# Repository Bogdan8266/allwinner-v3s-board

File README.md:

# allwinner-v3s-board
# allwinner-v3s-board

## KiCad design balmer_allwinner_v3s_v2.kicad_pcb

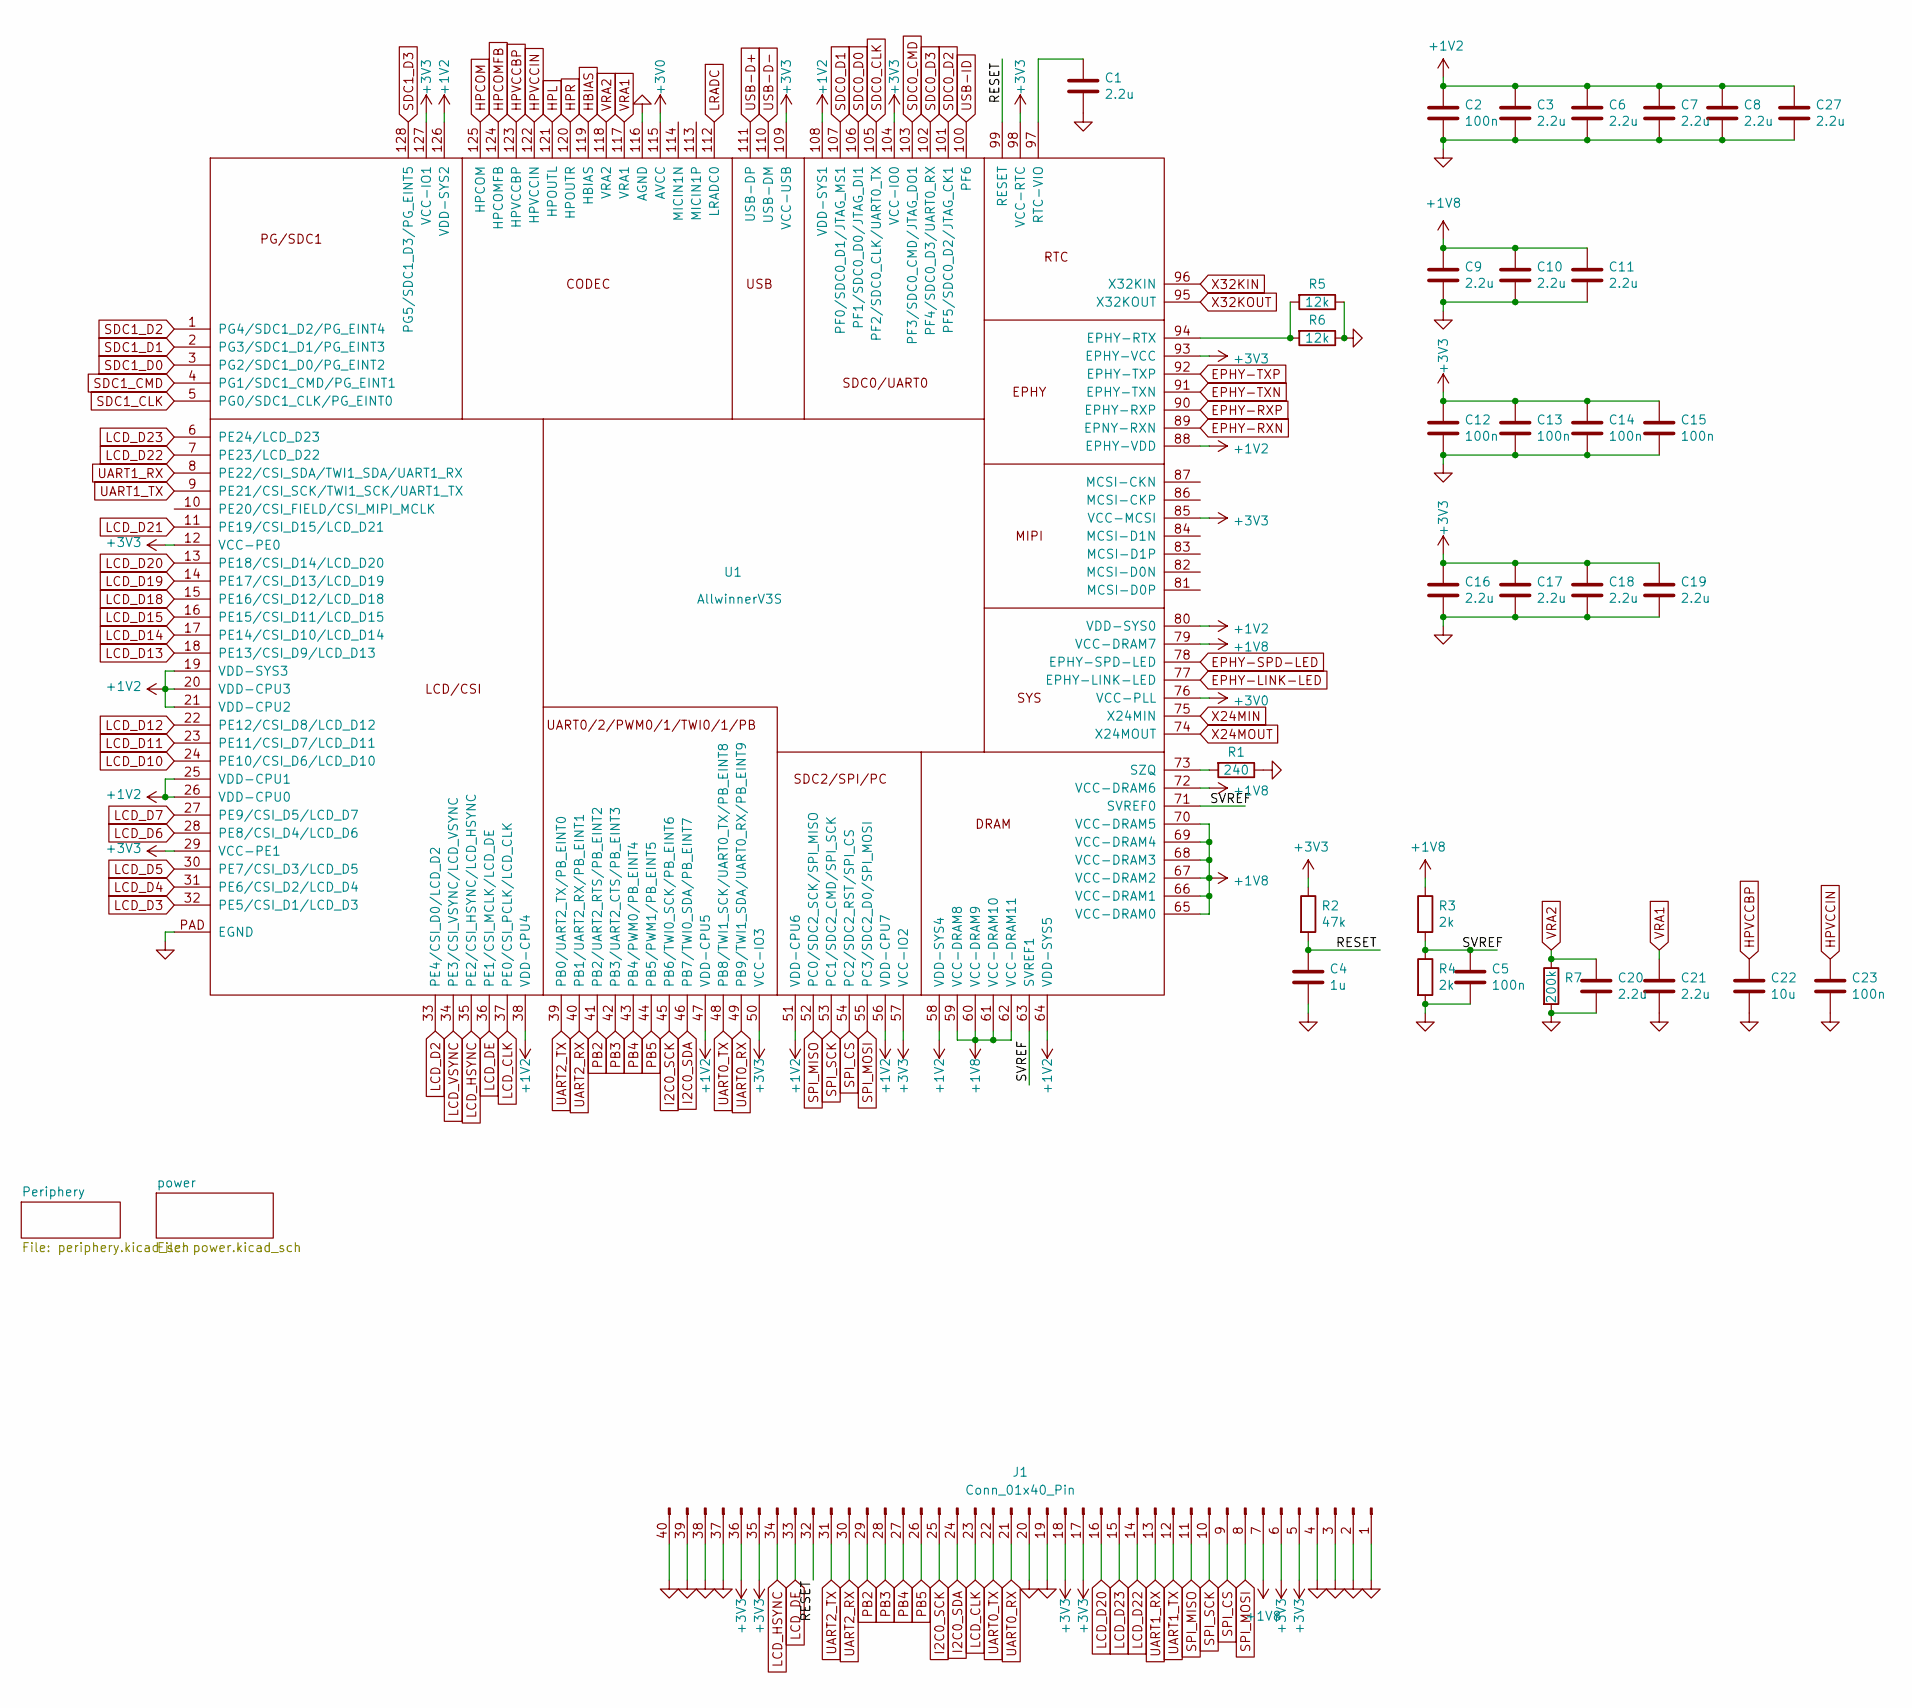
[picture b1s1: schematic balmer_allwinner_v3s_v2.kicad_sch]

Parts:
C1, C3, C6, C7, C8, C9, C10, C11, C16, C17, C18, C19, C20, C21, C27: 2.2u; C_0805_2012Metric
C2, C5, C12, C13, C14, C15, C23: 100n; C_0603_1608Metric
C4: 1u; C_0603_1608Metric
C22: 10u; C_0805_2012Metric
J1: Conn_01x40_Pin; DIP-40_100
R1: 240; R_0603_1608Metric
R2: 47k; R_0603_1608Metric
R3, R4: 2k; R_0603_1608Metric
R5, R6: 12k; R_0603_1608Metric
R7: 200k; R_0603_1608Metric
U1: AllwinnerV3S; eLQFP-128_14x14_Pitch0.4mm_EPAD_5.72mm

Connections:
+1V2: C2.1, C3.1, C6.1, C7.1, C8.1, C27.1, U1.19 (VDD-SYS3), U1.20 (VDD-CPU3), U1.21 (VDD-CPU2), U1.25 (VDD-CPU1), U1.26 (VDD-CPU0), U1.38 (VDD-CPU4), U1.47 (VDD-CPU5), U1.51 (VDD-CPU6), U1.56 (VDD-CPU7), U1.58 (VDD-SYS4), U1.64 (VDD-SYS5), U1.80 (VDD-SYS0), U1.88 (EPHY-VDD), U1.108 (VDD-SYS1), U1.126 (VDD-SYS2); also elsewhere on the board
+1V8: C9.1, C10.1, C11.1, J1.7, R3.1, U1.59 (VCC-DRAM8), U1.60 (VCC-DRAM9), U1.61 (VCC-DRAM10), U1.62 (VCC-DRAM11), U1.65 (VCC-DRAM0), U1.66 (VCC-DRAM1), U1.67 (VCC-DRAM2), U1.68 (VCC-DRAM3), U1.69 (VCC-DRAM4), U1.70 (VCC-DRAM5), U1.72 (VCC-DRAM6), U1.79 (VCC-DRAM7); also elsewhere on the board
+3V0: U1.76 (VCC-PLL), U1.115 (AVCC); also elsewhere on the board
+3V3: C12.1, C13.1, C14.1, C15.1, C16.1, C17.1, C18.1, C19.1, J1.5, J1.6, J1.17, J1.18, J1.35, J1.36, R2.1, U1.12 (VCC-PE0), U1.29 (VCC-PE1), U1.50 (VCC-IO3), U1.57 (VCC-IO2), U1.85 (VCC-MCSI), U1.93 (EPHY-VCC), U1.98 (VCC-RTC), U1.104 (VCC-IO0), U1.109 (VCC-USB), U1.127 (VCC-IO1); also elsewhere on the board
/RESET: C4.1, J1.32, R2.2, U1.99 (RESET)
/SVREF: C5.1, R3.2, R4.1, U1.63 (SVREF1), U1.71 (SVREF0)
EPHY-LINK-LED: U1.77 (EPHY-LINK-LED); also elsewhere on the board
EPHY-RXN: U1.89 (EPNY-RXN); also elsewhere on the board
EPHY-RXP: U1.90 (EPHY-RXP); also elsewhere on the board
EPHY-SPD-LED: U1.78 (EPHY-SPD-LED); also elsewhere on the board
EPHY-TXN: U1.91 (EPHY-TXN); also elsewhere on the board
EPHY-TXP: U1.92 (EPHY-TXP); also elsewhere on the board
GND: C1.2, C2.2, C3.2, C4.2, C5.2, C6.2, C7.2, C8.2, C9.2, C10.2, C11.2, C12.2, C13.2, C14.2, C15.2, C16.2, C17.2, C18.2, C19.2, C20.2, C21.2, C22.2, C23.2, C27.2, J1.1, J1.2, J1.3, J1.4, J1.19, J1.20, J1.37, J1.38, J1.39, J1.40, R1.1, R4.2, R5.1, R6.1, R7.2, U1.116 (AGND), U1.PAD (EGND); also elsewhere on the board
HBIAS: U1.119 (HBIAS); also elsewhere on the board
HPCOM: U1.125 (HPCOM); also elsewhere on the board
HPCOMFB: U1.124 (HPCOMFB); also elsewhere on the board
HPL: U1.121 (HPOUTL); also elsewhere on the board
HPR: U1.120 (HPOUTR); also elsewhere on the board
HPVCCBP: C22.1, U1.123 (HPVCCBP)
HPVCCIN: C23.1, U1.122 (HPVCCIN)
I2C0_SCK: J1.25, U1.45 (PB6/TWI0_SCK/PB_EINT6)
I2C0_SDA: J1.24, U1.46 (PB7/TWI0_SDA/PB_EINT7)
LCD_CLK: J1.23, U1.37 (PE0/CSI_PCLK/LCD_CLK)
LCD_D2: U1.33 (PE4/CSI_D0/LCD_D2)
LCD_D3: U1.32 (PE5/CSI_D1/LCD_D3)
LCD_D4: U1.31 (PE6/CSI_D2/LCD_D4)
LCD_D5: U1.30 (PE7/CSI_D3/LCD_D5)
LCD_D6: U1.28 (PE8/CSI_D4/LCD_D6)
LCD_D7: U1.27 (PE9/CSI_D5/LCD_D7)
LCD_D10: U1.24 (PE10/CSI_D6/LCD_D10)
LCD_D11: U1.23 (PE11/CSI_D7/LCD_D11)
LCD_D12: U1.22 (PE12/CSI_D8/LCD_D12)
LCD_D13: U1.18 (PE13/CSI_D9/LCD_D13)
LCD_D14: U1.17 (PE14/CSI_D10/LCD_D14)
LCD_D15: U1.16 (PE15/CSI_D11/LCD_D15)
LCD_D18: U1.15 (PE16/CSI_D12/LCD_D18)
LCD_D19: U1.14 (PE17/CSI_D13/LCD_D19)
LCD_D20: J1.16, U1.13 (PE18/CSI_D14/LCD_D20)
LCD_D21: U1.11 (PE19/CSI_D15/LCD_D21)
LCD_D22: J1.14, U1.7 (PE23/LCD_D22)
LCD_D23: J1.15, U1.6 (PE24/LCD_D23)
LCD_DE: J1.33, U1.36 (PE1/CSI_MCLK/LCD_DE)
LCD_HSYNC: J1.34, U1.35 (PE2/CSI_HSYNC/LCD_HSYNC)
LCD_VSYNC: U1.34 (PE3/CSI_VSYNC/LCD_VSYNC)
LRADC: U1.112 (LRADC0); also elsewhere on the board
unnamed: R5.2, R6.2, U1.94 (EPHY-RTX)
unnamed: C1.1, U1.97 (RTC-VIO)
unnamed: R1.2, U1.73 (SZQ)
PB2: J1.29, U1.41 (PB2/UART2_RTS/PB_EINT2)
PB3: J1.28, U1.42 (PB3/UART2_CTS/PB_EINT3)
PB4: J1.27, U1.43 (PB4/PWM0/PB_EINT4)
PB5: J1.26, U1.44 (PB5/PWM1/PB_EINT5)
SDC0_CLK: U1.105 (PF2/SDC0_CLK/UART0_TX); also elsewhere on the board
SDC0_CMD: U1.103 (PF3/SDC0_CMD/JTAG_DO1); also elsewhere on the board
SDC0_D0: U1.106 (PF1/SDC0_D0/JTAG_DI1); also elsewhere on the board
SDC0_D1: U1.107 (PF0/SDC0_D1/JTAG_MS1); also elsewhere on the board
SDC0_D2: U1.101 (PF5/SDC0_D2/JTAG_CK1); also elsewhere on the board
SDC0_D3: U1.102 (PF4/SDC0_D3/UART0_RX); also elsewhere on the board
SDC1_CLK: U1.5 (PG0/SDC1_CLK/PG_EINT0)
SDC1_CMD: U1.4 (PG1/SDC1_CMD/PG_EINT1)
SDC1_D0: U1.3 (PG2/SDC1_D0/PG_EINT2)
SDC1_D1: U1.2 (PG3/SDC1_D1/PG_EINT3)
SDC1_D2: U1.1 (PG4/SDC1_D2/PG_EINT4)
SDC1_D3: U1.128 (PG5/SDC1_D3/PG_EINT5)
SPI_CS: J1.9, U1.54 (PC2/SDC2_RST/SPI_CS)
SPI_MISO: J1.11, U1.52 (PC0/SDC2_SCK/SPI_MISO)
SPI_MOSI: J1.8, U1.55 (PC3/SDC2_D0/SPI_MOSI)
SPI_SCK: J1.10, U1.53 (PC1/SDC2_CMD/SPI_SCK)
UART0_RX: J1.21, U1.49 (PB9/TWI1_SDA/UART0_RX/PB_EINT9)
UART0_TX: J1.22, U1.48 (PB8/TWI1_SCK/UART0_TX/PB_EINT8)
UART1_RX: J1.13, U1.8 (PE22/CSI_SDA/TWI1_SDA/UART1_RX)
UART1_TX: J1.12, U1.9 (PE21/CSI_SCK/TWI1_SCK/UART1_TX)
UART2_RX: J1.30, U1.40 (PB1/UART2_RX/PB_EINT1)
UART2_TX: J1.31, U1.39 (PB0/UART2_TX/PB_EINT0)
USB-D+: U1.111 (USB-DP); also elsewhere on the board
USB-D-: U1.110 (USB-DM); also elsewhere on the board
USB-ID: U1.100 (PF6)
VRA1: C21.1, U1.117 (VRA1)
VRA2: C20.1, R7.1, U1.118 (VRA2)
X24MIN: U1.75 (X24MIN); also elsewhere on the board
X24MOUT: U1.74 (X24MOUT); also elsewhere on the board
X32KIN: U1.96 (X32KIN); also elsewhere on the board
X32KOUT: U1.95 (X32KOUT); also elsewhere on the board

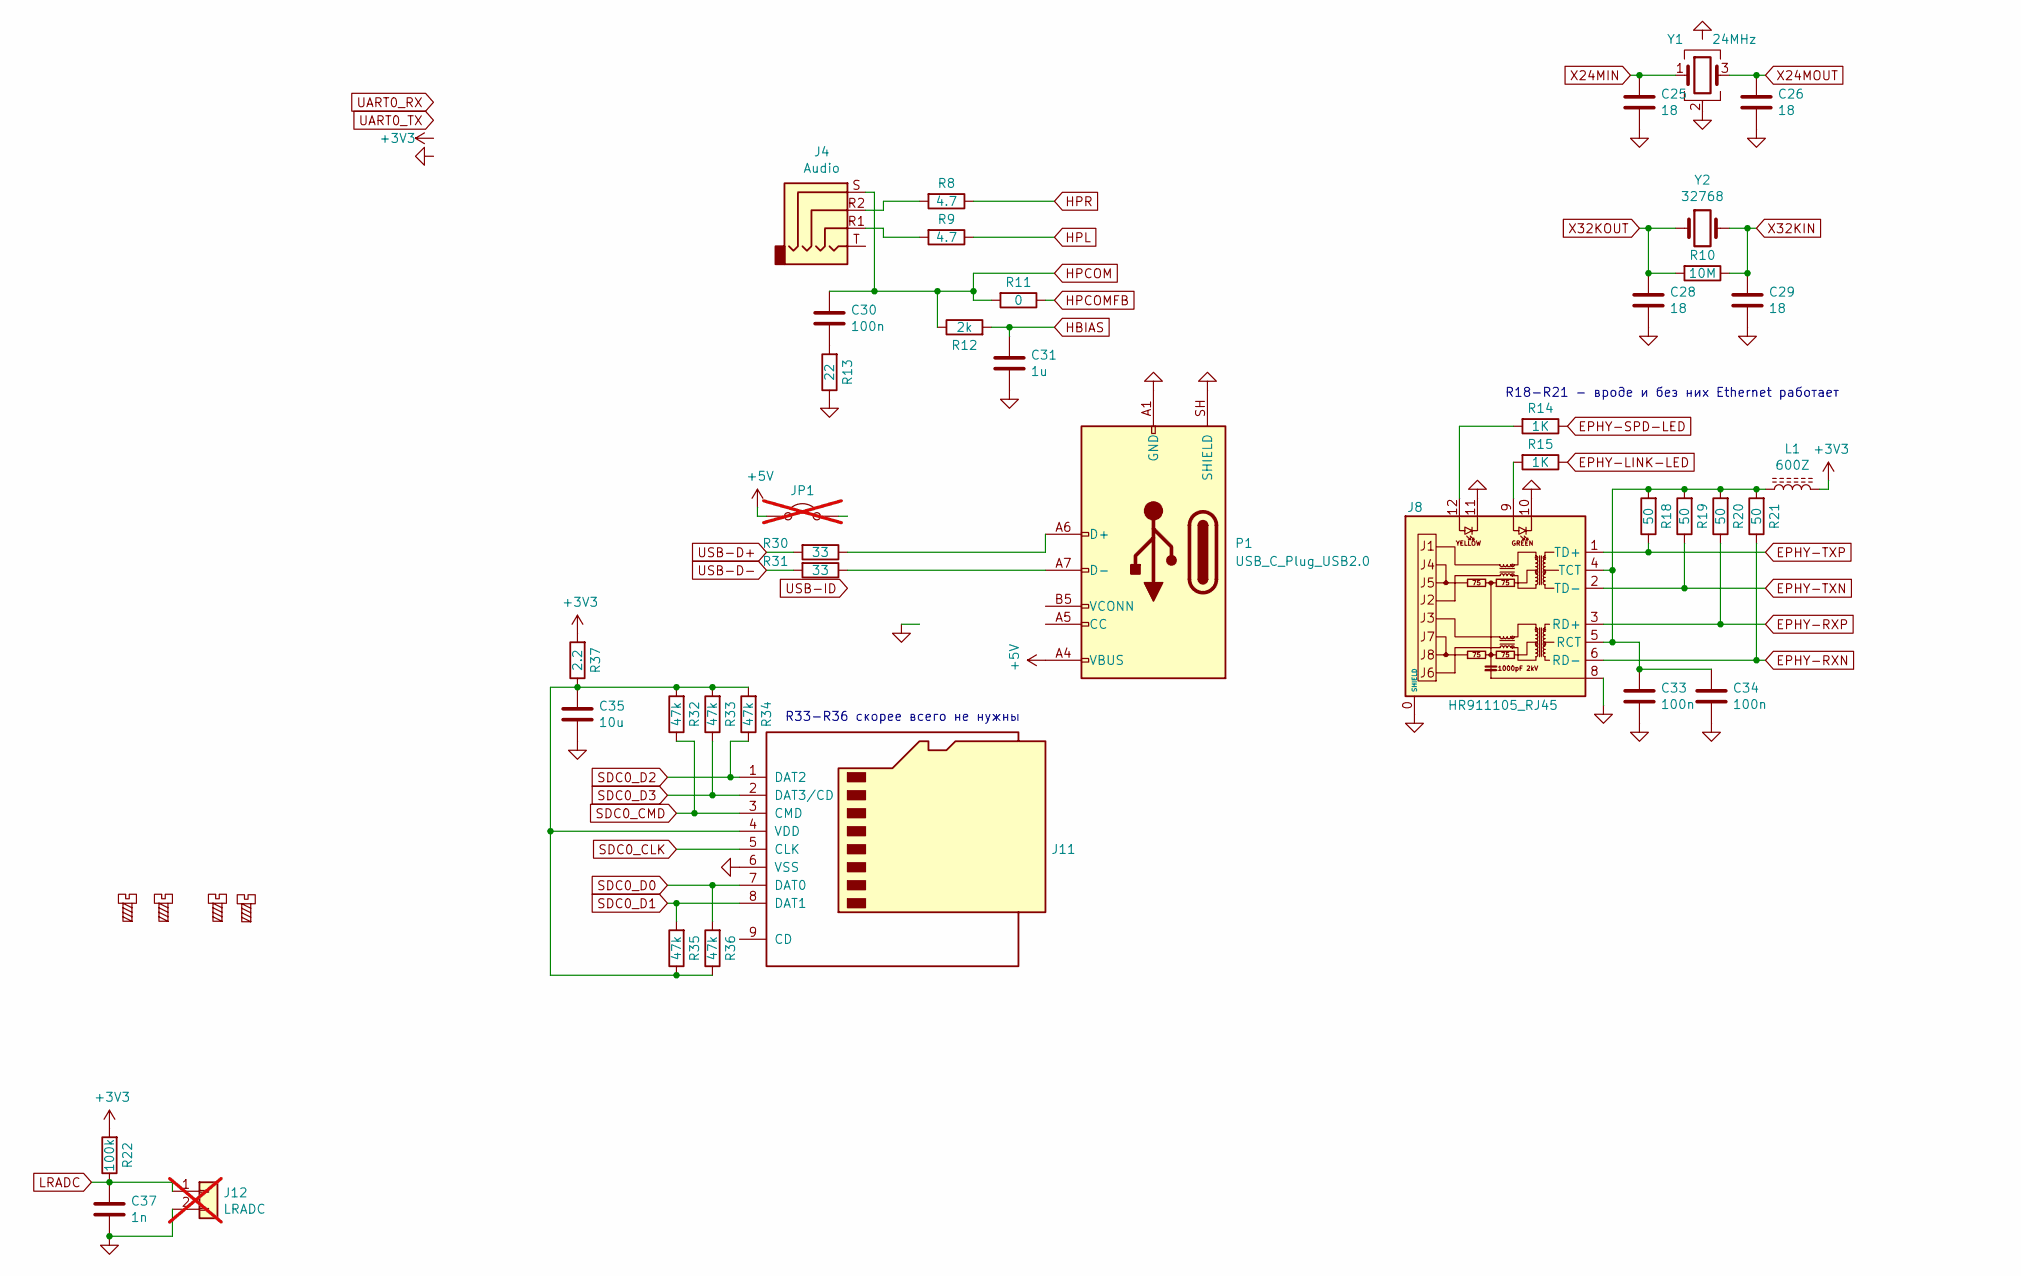
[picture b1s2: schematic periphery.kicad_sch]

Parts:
C25, C26, C28, C29: 18; C_0603_1608Metric
C30, C33, C34: 100n; C_0603_1608Metric
C31: 1u; C_0603_1608Metric
C35: 10u; C_1206_3216Metric
C37: 1n; C_0603_1608Metric
H1, H2, H3, H4: MountingScrew; MountingHole_2.5mm_Pad_Via
J4: Audio; Jack_3.5mm_PJ311_Horizontal
J8: HR911105_RJ45; HANRUN_HR911105A
J11: Micro_SD_Card_Ebay; microSD_HC_Wuerth_693072010801
J12: LRADC; PinSocket_1x02_P1.27mm_Vertical; not fitted
JP1: Jumper_2_Open; PinHeader_1x02_P2.00mm_Vertical; not fitted
L1: 600Z; L_1206_3216Metric
P1: USB_C_Plug_USB2.0; USB_C_Receptacle_G-Switch_GT-USB-7010ASV
R8, R9: 4.7; R_0603_1608Metric
R10: 10M; R_0805_2012Metric
R11: 0; R_0603_1608Metric
R12: 2k; R_0603_1608Metric
R13: 22; R_0603_1608Metric
R14, R15: 1K; R_0603_1608Metric
R18, R19, R20, R21: 50; R_0603_1608Metric
R22: 100k; R_0603_1608Metric
R30, R31: 33; R_0603_1608Metric
R32, R33, R34, R35, R36: 47k; R_0603_1608Metric
R37: 2.2; R_0805_2012Metric
Y1: 24MHz; Crystal_SMD_3225-4Pin_3.2x2.5mm
Y2: 32768; Crystal_C26-LF_D2.1mm_L6.5mm_Horizontal

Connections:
+3V3: L1.2, R22.2, R37.2; also elsewhere on the board
+5V: JP1.1 (A), P1.A4 (VBUS), P1.A9 (VBUS), P1.B4 (VBUS), P1.B9 (VBUS); also elsewhere on the board
EPHY-LINK-LED: R15.1; also elsewhere on the board
EPHY-RXN: J8.6 (RD-), R21.1; also elsewhere on the board
EPHY-RXP: J8.3 (RD+), R20.1; also elsewhere on the board
EPHY-SPD-LED: R14.1; also elsewhere on the board
EPHY-TXN: J8.2 (TD-), R19.1; also elsewhere on the board
EPHY-TXP: J8.1 (TD+), R18.1; also elsewhere on the board
GND: C25.2, C26.2, C28.2, C29.2, C31.2, C33.2, C34.2, C35.2, C37.2, J8.0 (SHIELD), J8.8, J8.10, J8.11, J11.6 (VSS), J12.2, P1.A1 (GND), P1.A12 (GND), P1.B1 (GND), P1.B12 (GND), P1.SH (SHIELD), R13.1, Y1.2 (G), Y1.4 (G); also elsewhere on the board
HBIAS: C31.1, R12.2; also elsewhere on the board
HPCOM: C30.1, J4.S, R11.2, R12.1; also elsewhere on the board
HPCOMFB: R11.1; also elsewhere on the board
HPL: R9.1; also elsewhere on the board
HPR: R8.1; also elsewhere on the board
LRADC: C37.1, J12.1, R22.1; also elsewhere on the board
unnamed: C30.2, R13.2
unnamed: J4.R1, R9.2
unnamed: J4.R2, R8.2
unnamed: C33.1, C34.1, J8.4 (TCT), J8.5 (RCT), L1.1, R18.2, R19.2, R20.2, R21.2
unnamed: J8.9, R15.2
unnamed: J8.12, R14.2
unnamed: C35.1, J11.4 (VDD), R32.2, R33.2, R34.2, R35.1, R36.1, R37.1
unnamed: P1.A6 (D+), R30.1
unnamed: P1.A7 (D-), R31.1
SDC0_CLK: J11.5 (CLK); also elsewhere on the board
SDC0_CMD: J11.3 (CMD), R32.1; also elsewhere on the board
SDC0_D0: J11.7 (DAT0), R36.2; also elsewhere on the board
SDC0_D1: J11.8 (DAT1), R35.2; also elsewhere on the board
SDC0_D2: J11.1 (DAT2), R34.1; also elsewhere on the board
SDC0_D3: J11.2 (DAT3/CD), R33.1; also elsewhere on the board
USB-D+: R30.2; also elsewhere on the board
USB-D-: R31.2; also elsewhere on the board
X24MIN: C25.1, Y1.1; also elsewhere on the board
X24MOUT: C26.1, Y1.3; also elsewhere on the board
X32KIN: C29.1, R10.1, Y2.2; also elsewhere on the board
X32KOUT: C28.1, R10.2, Y2.1; also elsewhere on the board

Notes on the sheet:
R33-R36 скорее всего не нужны
R18-R21 - вроде и без них Ethernet работает

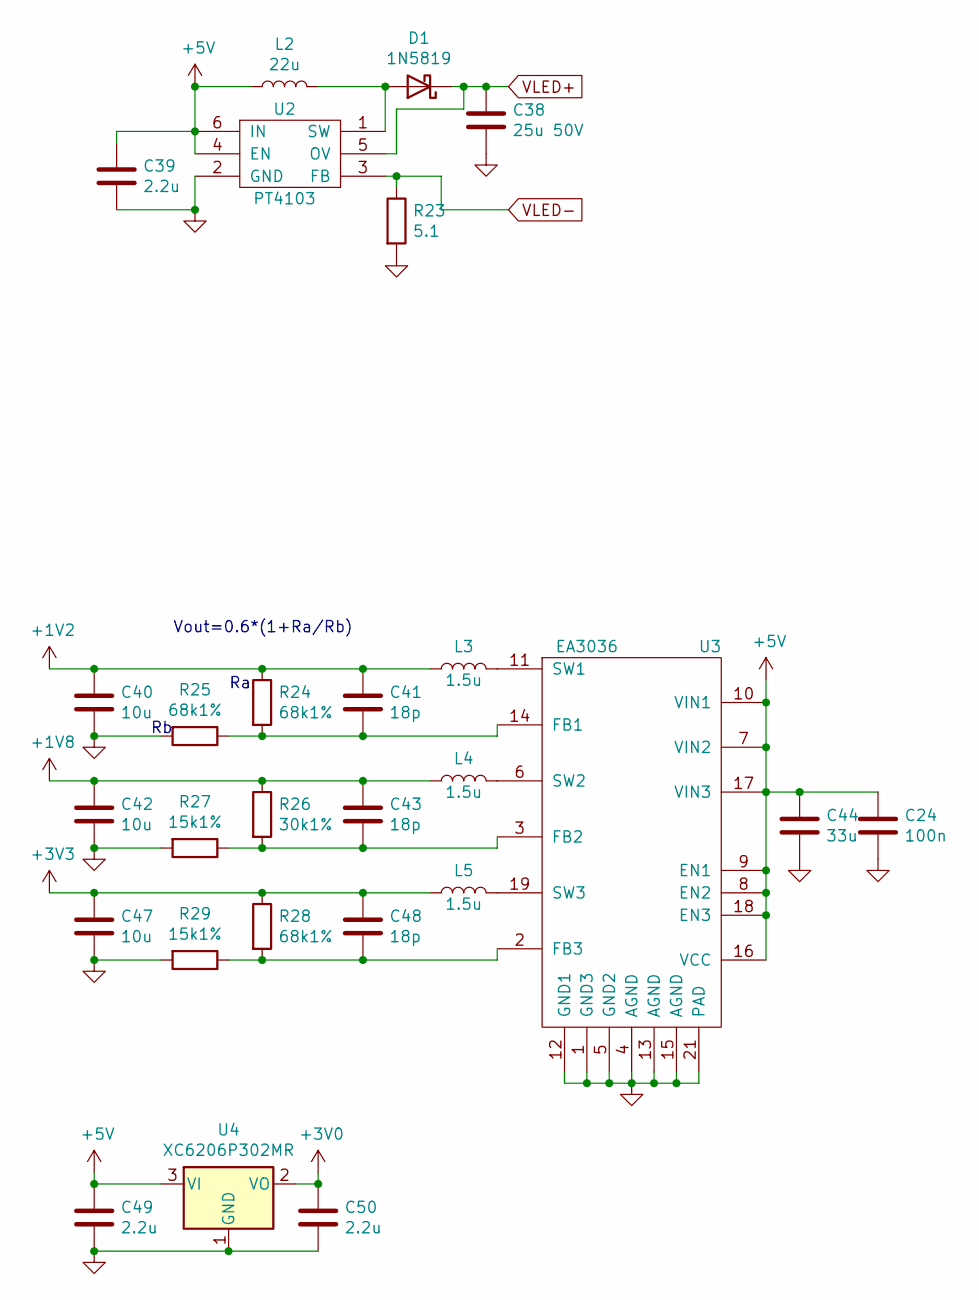
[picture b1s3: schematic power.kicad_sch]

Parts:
C24: 100n; C_0603_1608Metric
C38: 25u 50V; C_1206_3216Metric
C39, C49, C50: 2.2u; C_0805_2012Metric
C40, C42, C47: 10u; C_0805_2012Metric
C41, C43, C48: 18p; C_0603_1608Metric
C44: 33u; C_1206_3216Metric
D1: 1N5819; D_SOD-123
L2: 22u; L_Taiyo-Yuden_NR-60xx
L3, L4, L5: 1.5u; L_TDK_SLF6045
R23: 5.1; R_0603_1608Metric
R24, R25, R28: 68k1%; R_0603_1608Metric
R26: 30k1%; R_0603_1608Metric
R27, R29: 15k1%; R_0603_1608Metric
U2: PT4103; SOT-23-6
U3: EA3036; QFN-20-1EP_3x3mm_P0.4mm_EP1.65x1.65mm_ThermalVias
U4: XC6206P302MR; SOT-23

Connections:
+1V2: C40.1, C41.1, L3.1, R24.1; also elsewhere on the board
+1V8: C42.1, C43.1, L4.1, R26.1; also elsewhere on the board
+3V0: C50.1, U4.2 (VO); also elsewhere on the board
+3V3: C47.1, C48.1, L5.1, R28.1; also elsewhere on the board
+5V: C24.1, C39.1, C44.1, C49.1, L2.1, U2.4 (EN), U2.6 (IN), U3.7 (VIN2), U3.8 (EN2), U3.9 (EN1), U3.10 (VIN1), U3.16 (VCC), U3.17 (VIN3), U3.18 (EN3), U4.3 (VI); also elsewhere on the board
GND: C24.2, C38.2, C39.2, C40.2, C42.2, C44.2, C47.2, C49.2, C50.2, R23.2, R25.2, R27.2, R29.2, U2.2 (GND), U3.1 (GND3), U3.4 (AGND), U3.5 (GND2), U3.12 (GND1), U3.13 (AGND), U3.15 (AGND), U3.21 (PAD), U4.1 (GND); also elsewhere on the board
unnamed: D1.2 (A), L2.2, U2.1 (SW)
unnamed: C41.2, R24.2, R25.1, U3.14 (FB1)
unnamed: C43.2, R26.2, R27.1, U3.3 (FB2)
unnamed: C48.2, R28.2, R29.1, U3.2 (FB3)
unnamed: L3.2, U3.11 (SW1)
unnamed: L4.2, U3.6 (SW2)
unnamed: L5.2, U3.19 (SW3)
VLED+: C38.1, D1.1 (K), U2.5 (OV)
VLED-: R23.1, U2.3 (FB)

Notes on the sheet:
Vout=0.6*(1+Ra/Rb)

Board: 2 copper layers, 101 parts (47 on the bottom side), 77 nets, no tracks yet.
